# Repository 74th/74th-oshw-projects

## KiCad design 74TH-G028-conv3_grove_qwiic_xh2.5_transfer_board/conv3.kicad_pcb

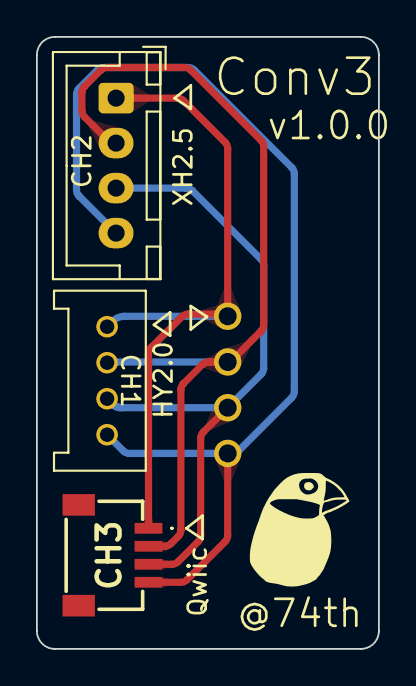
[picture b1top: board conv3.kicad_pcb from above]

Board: 2 copper layers, 19.0 x 34.0 mm, 4 parts (0 on the bottom side), 4 nets.

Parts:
CH1: 4Pin; HY2.0_Socket_TH_4Pin
CH2: 4Pin; JST_XH_B4B-XH-A_1x04_P2.50mm_Vertical
CH3: 4Pin; Qwick_connector
CH4: 4Pin

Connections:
/1: CH1.1, CH2.1, CH3.1, CH4.1
/2: CH1.2, CH2.2, CH3.2, CH4.2
/3: CH1.3, CH2.3, CH3.3, CH4.3
/4: CH1.4, CH2.4, CH3.4, CH4.4

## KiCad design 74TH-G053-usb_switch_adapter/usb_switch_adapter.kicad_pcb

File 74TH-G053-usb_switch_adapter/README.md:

# USB Switch Adapter

Switchable adapter for 5V USB-C devices that allows power shutdown with a switch.

スイッチで、電源遮断によるオフが行える 5V USB-C デバイスのアダプタ

🎥 https://twitter.com/74th/status/1823146532520239136

## feature

- Uses CH217 as the power switch.
- Can be used with CherryMX compatible switches or Kailh Choc Switches commonly used in custom keyboards, allowing for very light key presses.
- Pressing the switch can turn off the power. Additionally, holding down the switch can maintain the power-off state.
- Functions as a resettable fuse for overcurrent protection of 2A or higher. Overcurrent is indicated by LED flashing.
- Used WCH CH32V003J4M6 as the microcontroller. Various functionalities can be added by rewriting the firmware.

### 🇯🇵

- 電源スイッチとして、CH217 を使用。
- スイッチとして、自作キーボードで使われる CherryMX 互換スイッチ、または Kailh Choc Switch を使用可能で、非常に軽い力で押せるようにもできる。
- スイッチ押下で電源断ができる。さらにスイッチ長押しで電源断の状態を継続できる。
- 2A 以上の過電流によるリセッタフューズとしても機能する（2A）。過電流自は、LED が点滅する。
- 制御マイコンとして、WCH CH32V003J4M6 を使用。ファームウェアを書き換えることで、様々な機能を追加できる。

## 1.1.0

- Semantics [PDF](./usb_switch_adapter-semantics-1.1.0.pdf) [Kicanvas](https://kicanvas.org/?github=https%3A%2F%2Fgithub.com%2F74th%2F74th-oshw-projects%2Fblob%2F125ec0107b9b35aba094cce666c352a432412de6%2F74TH-G053-usb_switch_adapter%2Fusb_switch_adapter.kicad_sch)
- PCB [Kicanvas](https://kicanvas.org/?github=https%3A%2F%2Fgithub.com%2F74th%2F74th-oshw-projects%2Fblob%2Fusb-switch-adapter%2F1.1.0%2Fusb_switch_adapter%2Fusb_switch_adapter.kicad_pcb)

## BOM

| Reference | Name                                             | Quantity |
| --------- | ------------------------------------------------ | -------- |
| C1        | Capacitor 0603 100nF                             | 1        |
| D1        | LED 0805 Blue                                    | 1        |
| J1        | USB Type-C Receptacle                            | 1        |
| J2        | USB Type-C Receptacle                            | 1        |
| R1        | Register 0603 30kΩ                               | 1        |
| R2        | Register 0603 10kΩ                               | 1        |
| SW1       | Cheery MX Compatible Switch or Kailh Choc Switch | 1        |
| U1        | USB Power Protection IC SOT-23-6L CH217K         | 1        |
| U2        | MCU SOIC-8 WCH CH32V003J4M6                      | 1        |

## Firmware

- [./firmware/](./firmware/) using ch32v003fun

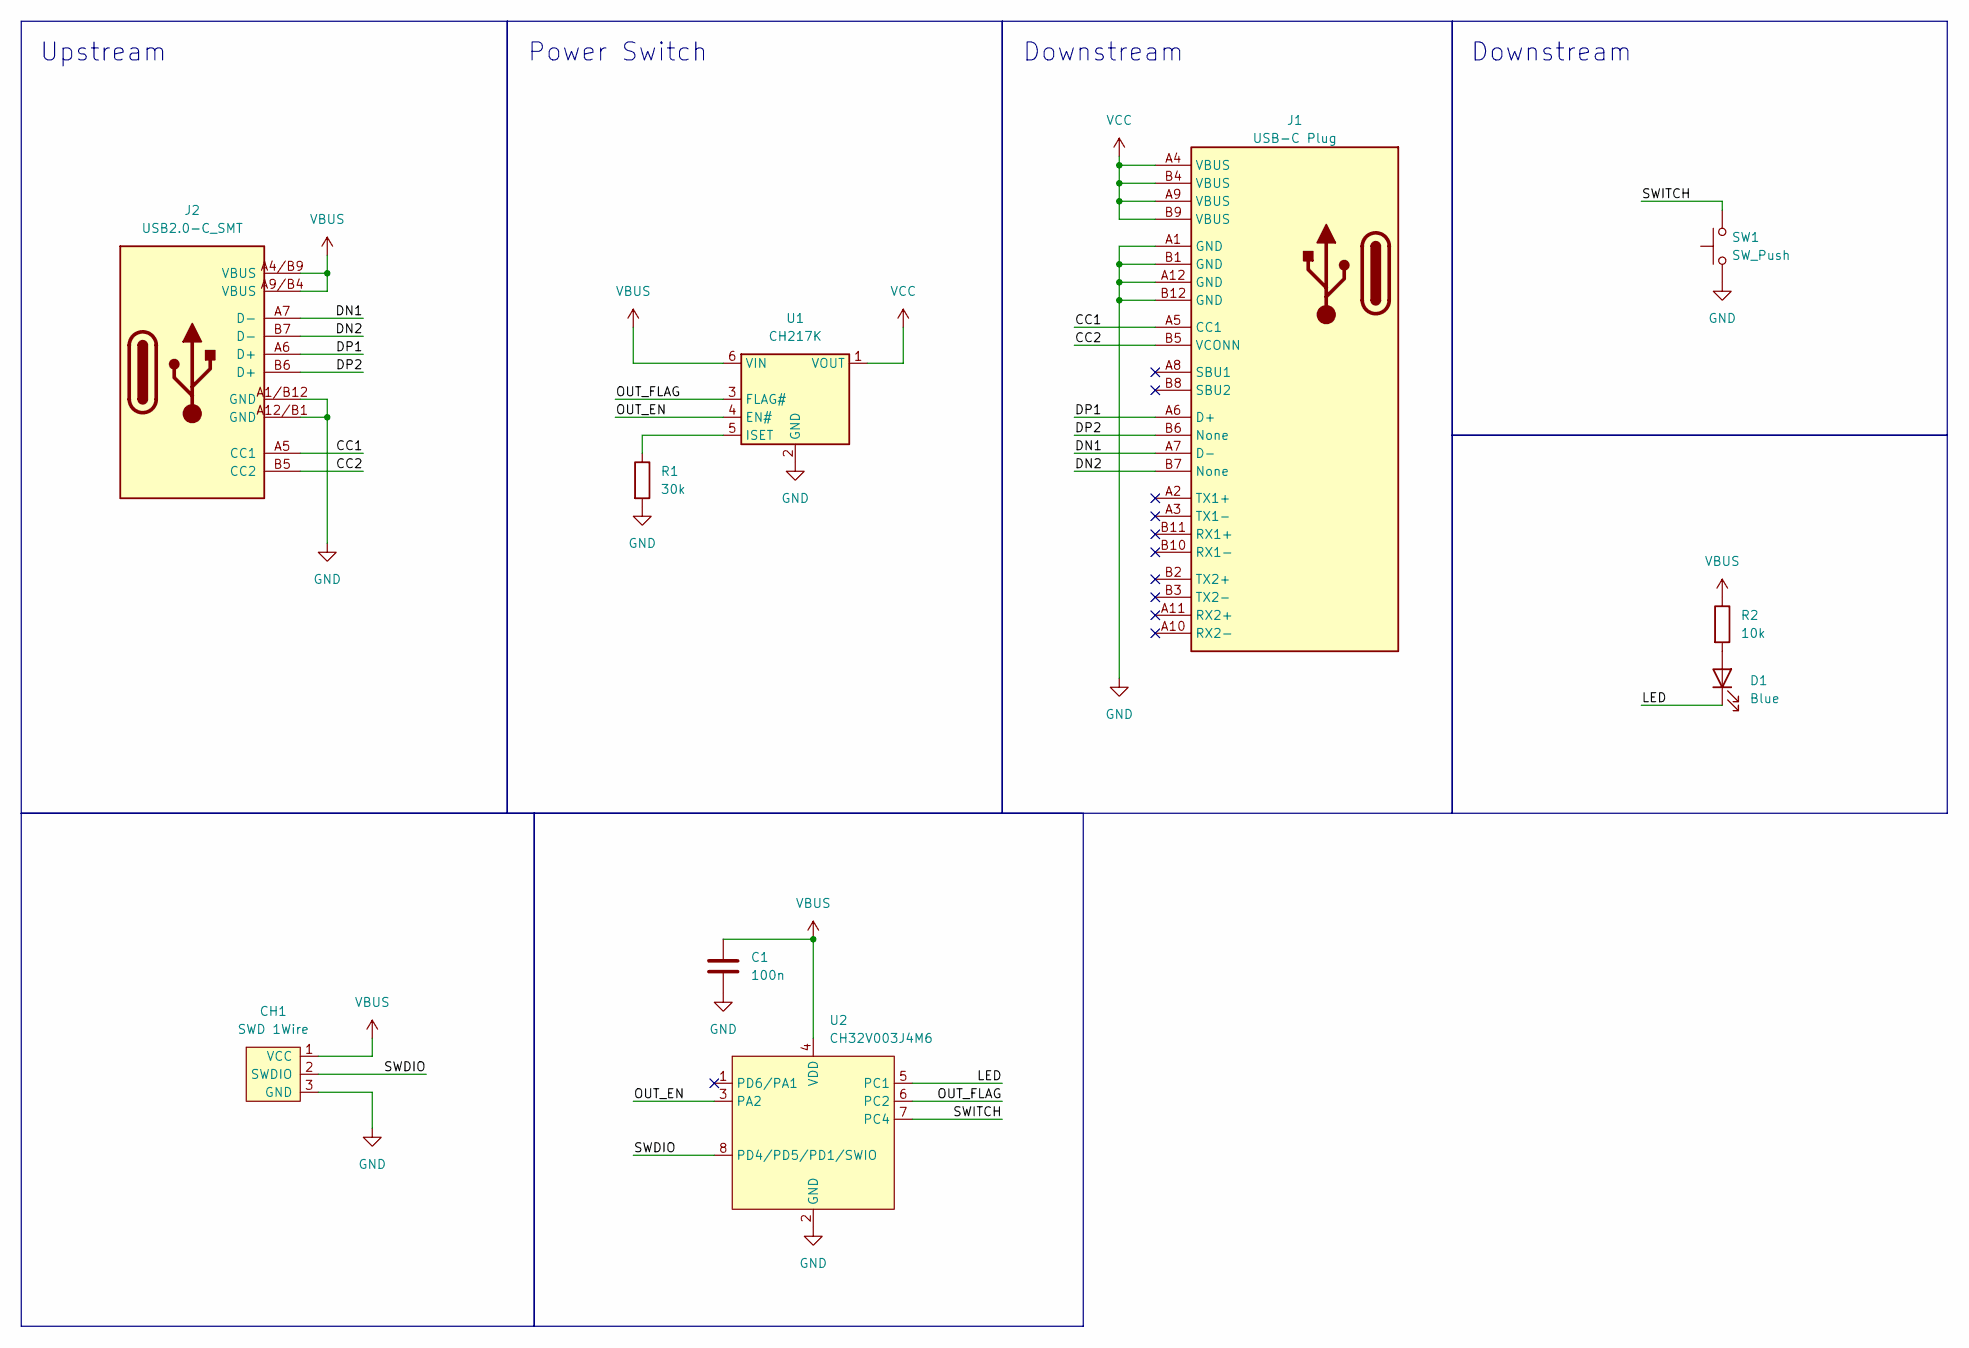
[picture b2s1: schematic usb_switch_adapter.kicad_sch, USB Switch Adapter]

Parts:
C1: 100n; Capacitor_0603_1608
CH1: SWD 1Wire; PinOut_Pin_3_3GND
D1: Blue; LED_BACK_0805_2012
J1: USB-C Plug; Connector_USB-C-Plug_24-Pin
J2: USB2.0-C_SMT; Connector_USB-C-Receptacle_SMT_12-Pin_MidMount
R1: 30k; Register_0603_1608
R2: 10k; Register_0603_1608
SW1: SW_Push; Switch_MXChoc_1.0u
U1: CH217K; Package_SOT-23-6
U2: CH32V003J4M6; Package_SOIC-8_3.9x4.9mm_P1.27mm

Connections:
/CC1: J1.A5 (CC1), J2.A5 (CC1)
/CC2: J1.B5 (VCONN), J2.B5 (CC2)
/DN1: J1.A7 (D-), J2.A7 (D-)
/DN2: J1.B7 (None), J2.B7 (D-)
/DP1: J1.A6 (D+), J2.A6 (D+)
/DP2: J1.B6 (None), J2.B6 (D+)
/LED: D1.1 (K), U2.5 (PC1)
/OUT_EN: U1.4 (EN#), U2.3 (PA2)
/OUT_FLAG: U1.3 (FLAG#), U2.6 (PC2)
/SWDIO: CH1.2 (SWDIO), U2.8 (PD4/PD5/PD1/SWIO)
/SWITCH: SW1.2, U2.7 (PC4)
/TXD: U2.1 (PD6/PA1)
GND: C1.2, CH1.3 (GND), J1.A1 (GND), J1.A12 (GND), J1.B1 (GND), J1.B12 (GND), J2.A1/B12 (GND), J2.A12/B1 (GND), R1.2, SW1.1, U1.2 (GND), U2.2 (GND)
unnamed: D1.2 (A), R2.2
unnamed: R1.1, U1.5 (ISET)
VBUS: C1.1, CH1.1 (VCC), J2.A4/B9 (VBUS), J2.A9/B4 (VBUS), R2.1, U1.6 (VIN), U2.4 (VDD)
VCC: J1.A4 (VBUS), J1.A9 (VBUS), J1.B4 (VBUS), J1.B9 (VBUS), U1.1 (VOUT)

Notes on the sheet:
Power Switch
Downstream
Upstream

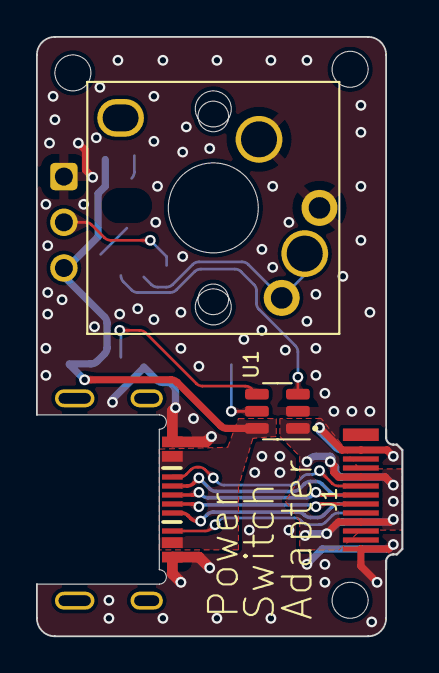
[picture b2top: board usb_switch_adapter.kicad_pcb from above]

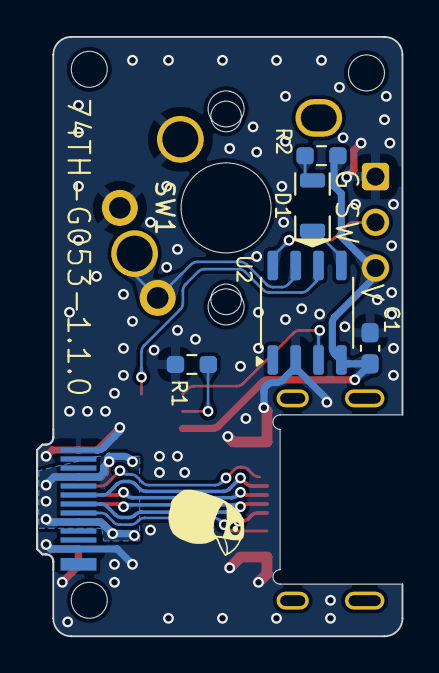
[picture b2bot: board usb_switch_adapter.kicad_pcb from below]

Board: 2 copper layers, 20.3 x 33.3 mm, 14 parts (6 on the bottom side), 16 nets.

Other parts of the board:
M2, M2#2, M2#3: Hole_M2_2.0
MISC-ICON: LOGO; Logo_74th_5mm

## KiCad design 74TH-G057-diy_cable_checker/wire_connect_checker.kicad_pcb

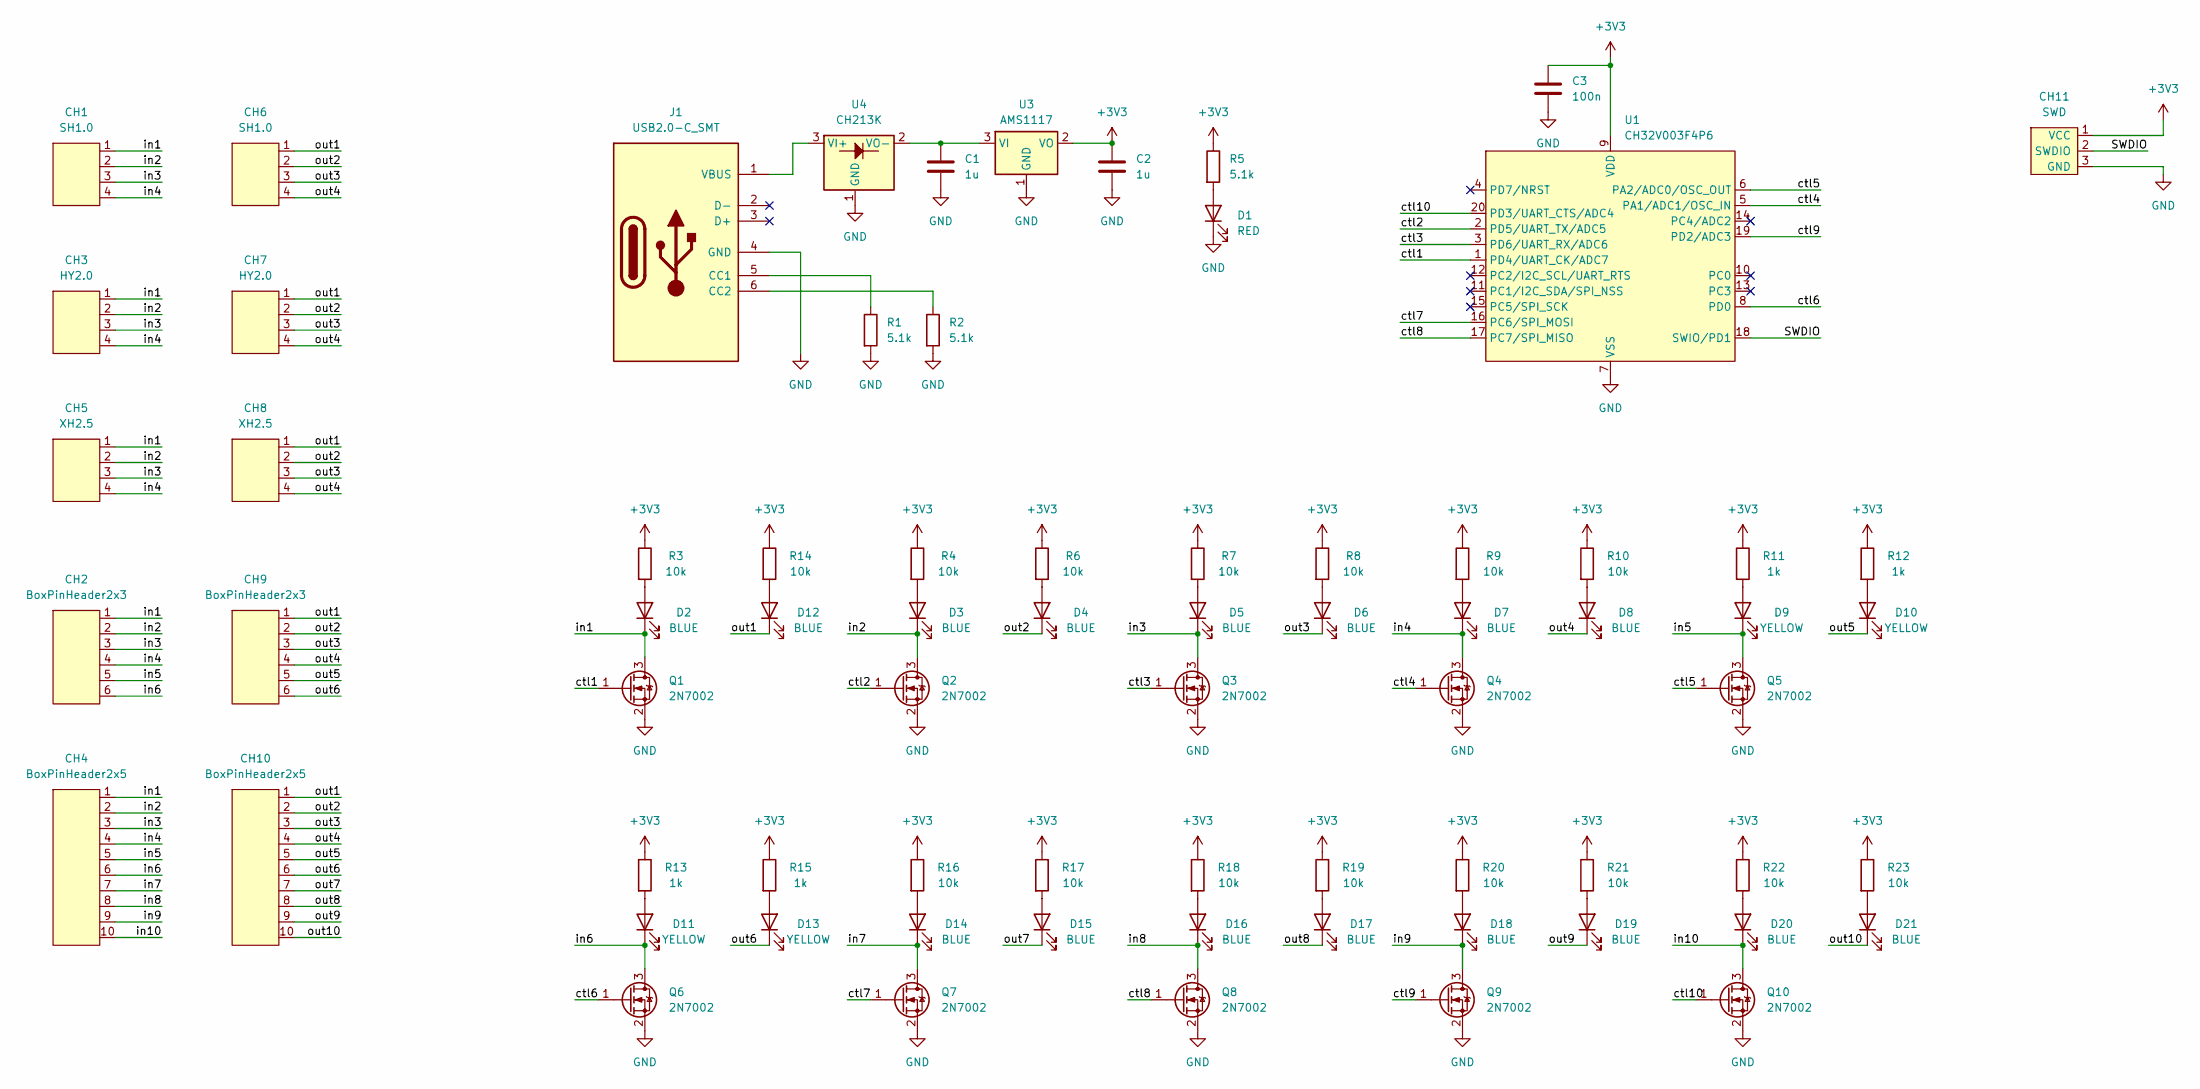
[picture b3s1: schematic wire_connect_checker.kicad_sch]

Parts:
C1, C2: 1u; Capacitor_0805_2012
C3: 100n; Capacitor_0805_2012
CH1, CH6: SH1.0; Connector_SH-1.0_SMD_4Pin
CH2, CH9: BoxPinHeader2x3; Connector_BoxPinHeader_2x03_P1.27mm
CH3, CH7: HY2.0; Connector_HY-2.0_TH-Vertical_4Pin
CH4, CH10: BoxPinHeader2x5; Connector_BoxPinHeader_2x05_P1.27mm
CH5, CH8: XH2.5; JST_XH_B4B-XH-AM_1x04_P2.50mm_Vertical
CH11: SWD; PinOut_Pin_3_3GND
D1: RED; LED_0805_2012
D2, D3, D4, D5, D6, D7, D8, D12, D14, D15, D16, D17, D18, D19, D20, D21: BLUE; LED_0805_2012
D9, D10, D11, D13: YELLOW; LED_0805_2012
J1: USB2.0-C_SMT; Connector_USB-C-Receptacle_SMT_12-Pin_Simple
Q1, Q2, Q3, Q4, Q5, Q6, Q7, Q8, Q9, Q10: 2N7002; Package_SOT-23
R1, R2, R5: 5.1k; Register_0805_2012
R3, R4, R6, R7, R8, R9, R10, R14, R16, R17, R18, R19, R20, R21, R22, R23: 10k; Register_0805_2012
R11, R12, R13, R15: 1k; Register_0805_2012
U1: CH32V003F4P6; Package_TSSOP-20_4.4x6.5mm_P0.65mm
U3: AMS1117; Package_SOT-89-3
U4: CH213K; Package_SOT-23

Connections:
+3V3: C2.1, C3.1, CH11.1 (VCC), R3.1, R4.1, R5.1, R6.1, R7.1, R8.1, R9.1, R10.1, R11.1, R12.1, R13.1, R14.1, R15.1, R16.1, R17.1, R18.1, R19.1, R20.1, R21.1, R22.1, R23.1, U1.9 (VDD), U3.2 (VO)
/SWDIO: CH11.2 (SWDIO), U1.18 (SWIO/PD1)
/ctl1: Q1.1 (G), U1.1 (PD4/UART_CK/ADC7)
/ctl2: Q2.1 (G), U1.2 (PD5/UART_TX/ADC5)
/ctl3: Q3.1 (G), U1.3 (PD6/UART_RX/ADC6)
/ctl4: Q4.1 (G), U1.5 (PA1/ADC1/OSC_IN)
/ctl5: Q5.1 (G), U1.6 (PA2/ADC0/OSC_OUT)
/ctl6: Q6.1 (G), U1.8 (PD0)
/ctl7: Q7.1 (G), U1.16 (PC6/SPI_MOSI)
/ctl8: Q8.1 (G), U1.17 (PC7/SPI_MISO)
/ctl9: Q9.1 (G), U1.19 (PD2/ADC3)
/ctl10: Q10.1 (G), U1.20 (PD3/UART_CTS/ADC4)
/in1: CH1.1, CH2.1, CH3.1, CH4.1, CH5.1, D2.1 (K), Q1.3 (D)
/in2: CH1.2, CH2.2, CH3.2, CH4.2, CH5.2, D3.1 (K), Q2.3 (D)
/in3: CH1.3, CH2.3, CH3.3, CH4.3, CH5.3, D5.1 (K), Q3.3 (D)
/in4: CH1.4, CH2.4, CH3.4, CH4.4, CH5.4, D7.1 (K), Q4.3 (D)
/in5: CH2.5, CH4.5, D9.1 (K), Q5.3 (D)
/in6: CH2.6, CH4.6, D11.1 (K), Q6.3 (D)
/in7: CH4.7, D14.1 (K), Q7.3 (D)
/in8: CH4.8, D16.1 (K), Q8.3 (D)
/in9: CH4.9, D18.1 (K), Q9.3 (D)
/in10: CH4.10, D20.1 (K), Q10.3 (D)
/out1: CH6.1, CH7.1, CH8.1, CH9.1, CH10.1, D12.1 (K)
/out2: CH6.2, CH7.2, CH8.2, CH9.2, CH10.2, D4.1 (K)
/out3: CH6.3, CH7.3, CH8.3, CH9.3, CH10.3, D6.1 (K)
/out4: CH6.4, CH7.4, CH8.4, CH9.4, CH10.4, D8.1 (K)
/out5: CH9.5, CH10.5, D10.1 (K)
/out6: CH9.6, CH10.6, D13.1 (K)
/out7: CH10.7, D15.1 (K)
/out8: CH10.8, D17.1 (K)
/out9: CH10.9, D19.1 (K)
/out10: CH10.10, D21.1 (K)
GND: C1.2, C2.2, C3.2, CH11.3 (GND), D1.1 (K), J1.4 (GND), Q1.2 (S), Q2.2 (S), Q3.2 (S), Q4.2 (S), Q5.2 (S), Q6.2 (S), Q7.2 (S), Q8.2 (S), Q9.2 (S), Q10.2 (S), R1.2, R2.2, U1.7 (VSS), U3.1 (GND), U4.1 (GND)
unnamed: D1.2 (A), R5.2
unnamed: D2.2 (A), R3.2
unnamed: D3.2 (A), R4.2
unnamed: D4.2 (A), R6.2
unnamed: D5.2 (A), R7.2
unnamed: D6.2 (A), R8.2
unnamed: D7.2 (A), R9.2
unnamed: D8.2 (A), R10.2
unnamed: D9.2 (A), R11.2
unnamed: D10.2 (A), R12.2
unnamed: D11.2 (A), R13.2
unnamed: D12.2 (A), R14.2
unnamed: D13.2 (A), R15.2
unnamed: D14.2 (A), R16.2
unnamed: D15.2 (A), R17.2
unnamed: D16.2 (A), R18.2
unnamed: D17.2 (A), R19.2
unnamed: D18.2 (A), R20.2
unnamed: D19.2 (A), R21.2
unnamed: D20.2 (A), R22.2
unnamed: D21.2 (A), R23.2
unnamed: J1.5 (CC1), R1.1
unnamed: J1.6 (CC2), R2.1
unnamed: J1.1 (VBUS), U4.3 (VI+)
unnamed: C1.1, U3.3 (VI), U4.2 (VO-)

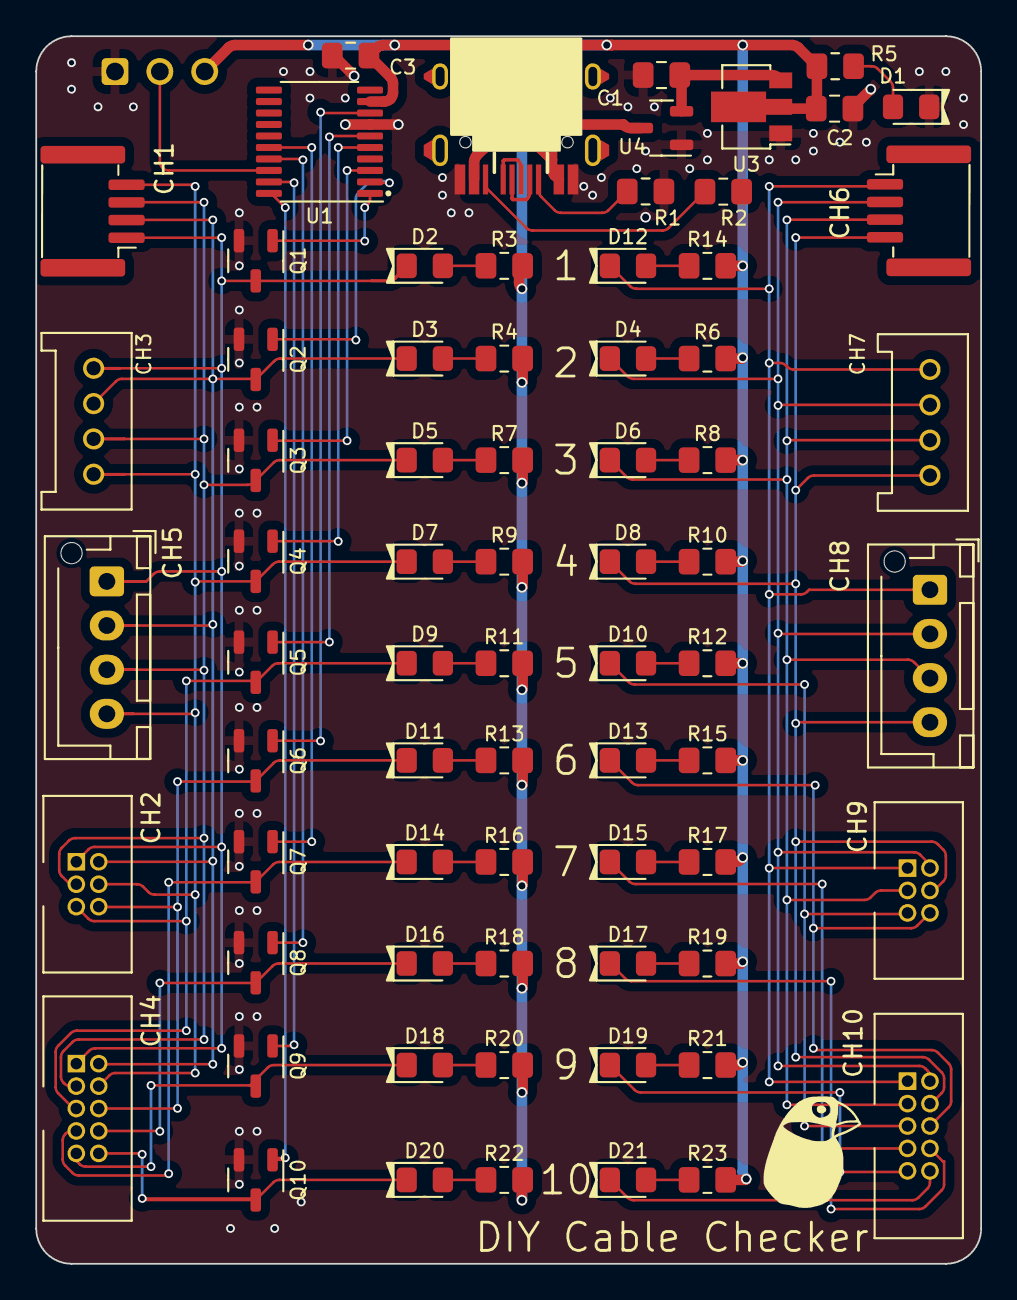
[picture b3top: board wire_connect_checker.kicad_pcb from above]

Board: 2 copper layers, 53.5 x 69.5 mm, 73 parts (0 on the bottom side), 58 nets.

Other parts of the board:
MISC-ICON: LOGO; 74th-7.5mm

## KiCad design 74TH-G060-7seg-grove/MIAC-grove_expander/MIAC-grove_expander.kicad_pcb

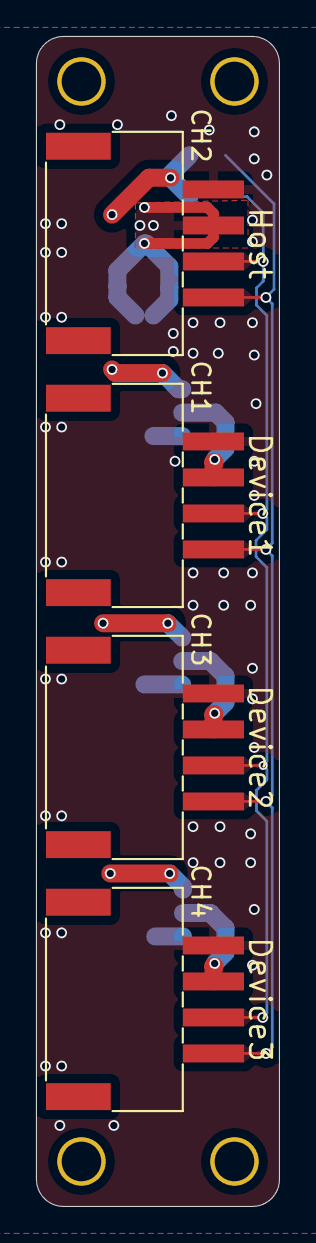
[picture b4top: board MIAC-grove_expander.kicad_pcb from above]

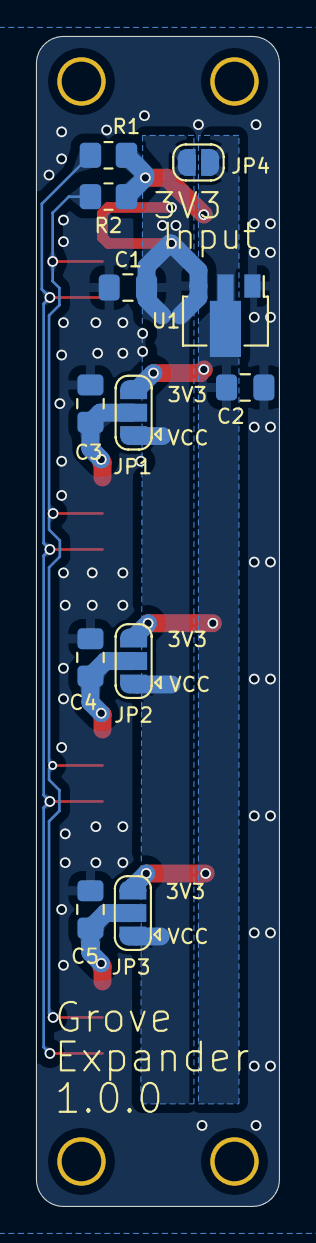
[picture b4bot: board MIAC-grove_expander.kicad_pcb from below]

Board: 2 copper layers, 13.5 x 65.0 mm, 20 parts (12 on the bottom side), 8 nets.

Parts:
C1, C2, C3, C4, C5: 22u; Capacitor_0805_2012
CH1: Device1; Connector_HY-2.0_SMD_4Pin
CH2: Host; Connector_HY-2.0_SMD_4Pin
CH3: Device2; Connector_HY-2.0_SMD_4Pin
CH4: Device3; Connector_HY-2.0_SMD_4Pin
JP1, JP2, JP3: Jumper_3_Open; SolderJumper-3
JP4: Jumper_2_Open; SolderJumper-2
M2, M2#2, M2#3, M2#4: M2_v2
R1, R2: 1k; Register_0805_2012
U1: AMS1117; Package_SOT-89-3

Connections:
+3V3: C2.1, JP1.3 (B), JP2.3 (B), JP3.3 (B), JP4.1 (A), R1.1, R2.1, U1.2 (VO)
/D1: CH1.1 (D0), CH2.1 (SCL), CH3.1 (D0), CH4.1 (D0), R1.2
/D2: CH1.2 (D1), CH2.2 (SDA), CH3.2 (D1), CH4.2 (D1), R2.2
GND: C1.2, C2.2, C3.2, C4.2, C5.2, CH1.4 (GND), CH2.4 (GND), CH3.4 (GND), CH4.4 (GND), U1.1 (GND)
unnamed: C3.1, CH1.3 (VCC), JP1.2 (C)
unnamed: C4.1, CH3.3 (VCC), JP2.2 (C)
unnamed: C5.1, CH4.3 (VCC), JP3.2 (C)
VCC: C1.1, CH2.3 (VCC), JP1.1 (A), JP2.1 (A), JP3.1 (A), JP4.2 (B), U1.3 (VI)

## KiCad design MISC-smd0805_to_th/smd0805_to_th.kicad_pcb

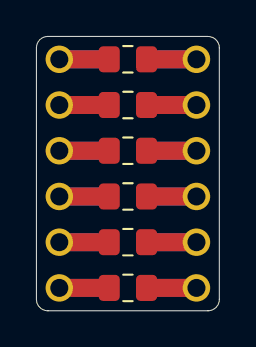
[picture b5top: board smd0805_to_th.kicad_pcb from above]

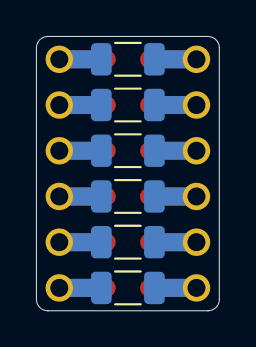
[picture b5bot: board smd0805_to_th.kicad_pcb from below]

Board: 2 copper layers, 10.2 x 15.2 mm, 14 parts (6 on the bottom side), 12 nets.

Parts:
CH1, CH2: Pin_6; PinOut_Pin_6
R1, R2, R3, R4, R5, R6: R; Capacitor_0805_2012
R7, R8, R9, R10, R11, R12: R; Capacitor_1206_3216

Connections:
unnamed: CH1.1, R1.1, R7.1
unnamed: CH1.2, R2.1, R8.1
unnamed: CH1.3, R3.1, R9.1
unnamed: CH1.4, R4.1, R10.1
unnamed: CH1.5, R5.1, R11.1
unnamed: CH1.6, R6.1, R12.1
unnamed: CH2.1, R1.2, R7.2
unnamed: CH2.2, R2.2, R8.2
unnamed: CH2.3, R3.2, R9.2
unnamed: CH2.4, R4.2, R10.2
unnamed: CH2.5, R5.2, R11.2
unnamed: CH2.6, R6.2, R12.2

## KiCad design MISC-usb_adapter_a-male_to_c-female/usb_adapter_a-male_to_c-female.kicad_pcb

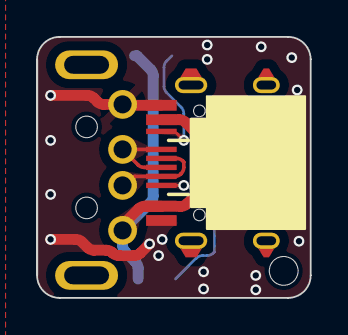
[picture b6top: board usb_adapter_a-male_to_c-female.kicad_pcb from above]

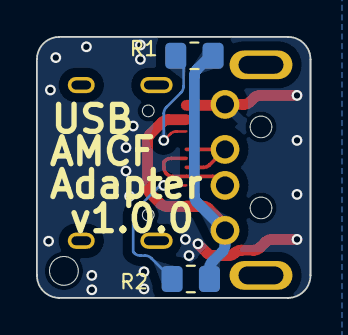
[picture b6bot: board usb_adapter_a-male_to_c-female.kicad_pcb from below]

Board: 2 copper layers, 15.2 x 14.5 mm, 5 parts (2 on the bottom side), 6 nets.

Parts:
J1: USB_TypeA-2.0_Plug; Connector_USB-A-Plug_TH
J2: USB2.0-C_SMT; Connector_USB-C-Receptacle_SMT_12-Pin_Simple
M2: Hole_M1.6_1.6
R1, R2: 56k; Register_0805_2012

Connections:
GND: J1.4 (GND), J2.4 (GND)
unnamed: J1.3 (D+), J2.3 (D+)
unnamed: J1.2 (D-), J2.2 (D-)
unnamed: J1.1 (VBUS), J2.1 (VBUS), R1.1, R2.1
unnamed: J2.5 (CC1), R2.2
unnamed: J2.6 (CC2), R1.2

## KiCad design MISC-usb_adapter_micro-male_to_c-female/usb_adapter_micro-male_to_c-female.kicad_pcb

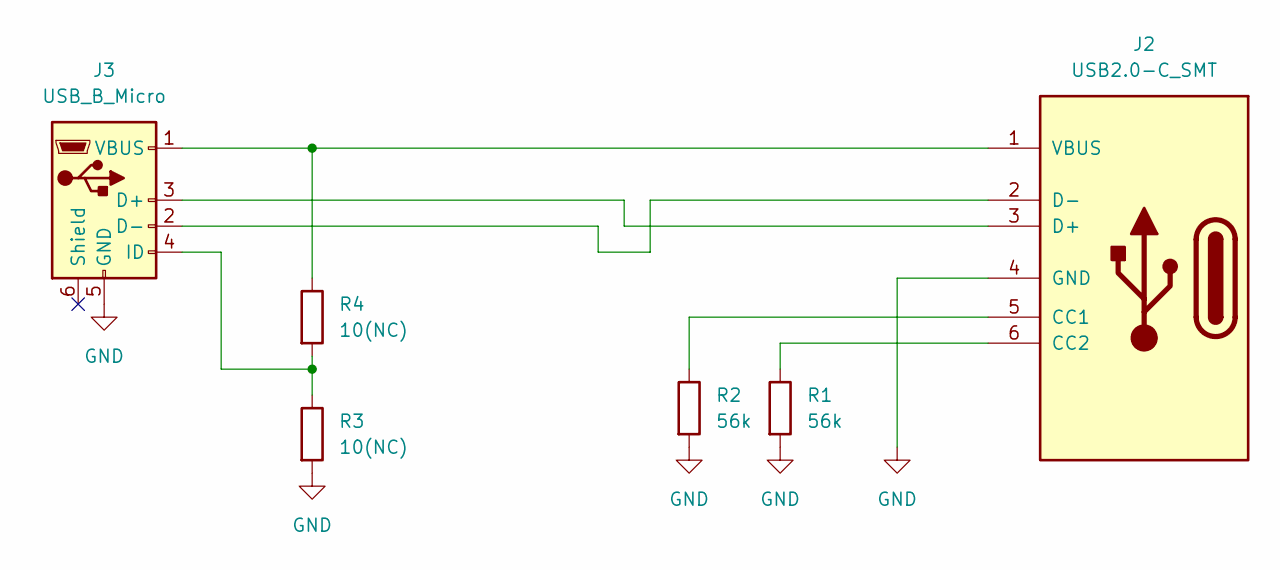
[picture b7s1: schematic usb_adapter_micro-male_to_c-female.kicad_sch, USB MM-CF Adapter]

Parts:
J2: USB2.0-C_SMT; Connector_USB-C-Receptacle_SMT_12-Pin_Simple
J3: USB_B_Micro; Connector_USB-Micro-Plug_SMD
R1, R2: 56k; Register_0603_1608
R3, R4: 10(NC); Register_0603_1608

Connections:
GND: J2.4 (GND), J3.5 (GND), R1.2, R2.2, R3.2
unnamed: J2.5 (CC1), R2.1
unnamed: J2.6 (CC2), R1.1
unnamed: J2.3 (D+), J3.3 (D+)
unnamed: J2.2 (D-), J3.2 (D-)
unnamed: J2.1 (VBUS), J3.1 (VBUS), R4.1
unnamed: J3.4 (ID), R3.1, R4.2

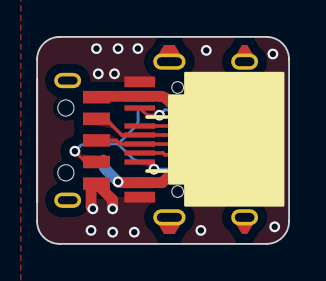
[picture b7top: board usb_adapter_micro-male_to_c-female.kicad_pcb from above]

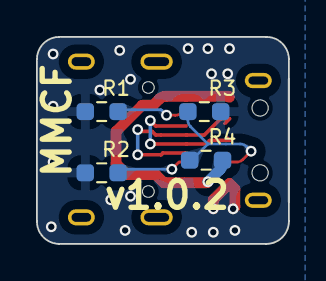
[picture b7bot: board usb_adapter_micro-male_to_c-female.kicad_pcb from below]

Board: 2 copper layers, 14.0 x 11.5 mm, 6 parts (4 on the bottom side), 7 nets.

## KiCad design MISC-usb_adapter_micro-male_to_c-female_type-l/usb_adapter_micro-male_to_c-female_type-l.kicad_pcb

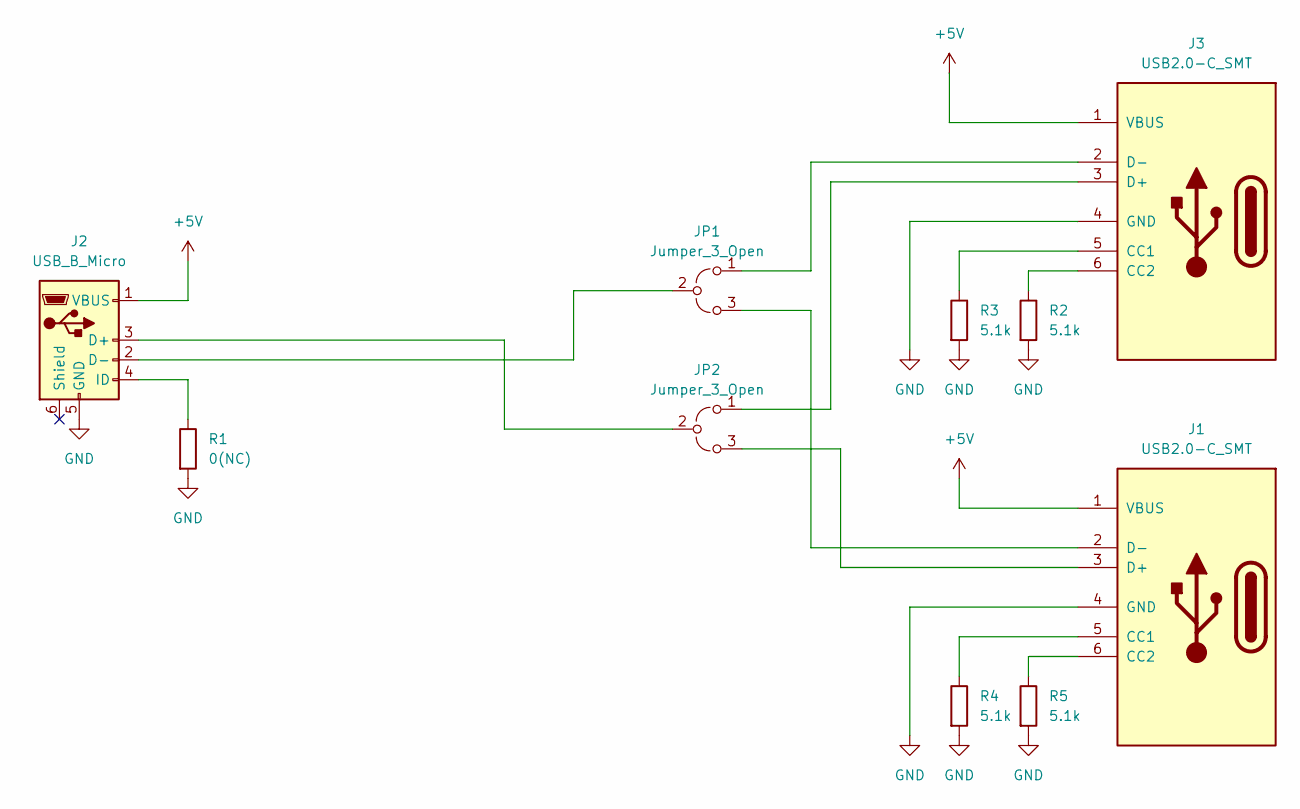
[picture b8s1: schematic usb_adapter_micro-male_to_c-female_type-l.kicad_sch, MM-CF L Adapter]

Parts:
J1, J3: USB2.0-C_SMT; Connector_USB-C-Receptacle_SMT_12-Pin_Simple
J2: USB_B_Micro; Connector_USB-Micro-Plug_SMD
JP1, JP2: Jumper_3_Open; SolderJumper-3_No1PinMark
R1: 0(NC); Register_0603_1608
R2, R3, R4, R5: 5.1k; Register_0603_1608

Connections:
+5V: J1.1 (VBUS), J2.1 (VBUS), J3.1 (VBUS)
GND: J1.4 (GND), J2.5 (GND), J3.4 (GND), R1.2, R2.2, R3.2, R4.2, R5.2
unnamed: J1.5 (CC1), R4.1
unnamed: J1.6 (CC2), R5.1
unnamed: J1.3 (D+), JP2.3 (B)
unnamed: J1.2 (D-), JP1.3 (B)
unnamed: J2.3 (D+), JP2.2 (C)
unnamed: J2.2 (D-), JP1.2 (C)
unnamed: J2.4 (ID), R1.1
unnamed: J3.5 (CC1), R3.1
unnamed: J3.6 (CC2), R2.1
unnamed: J3.3 (D+), JP2.1 (A)
unnamed: J3.2 (D-), JP1.1 (A)

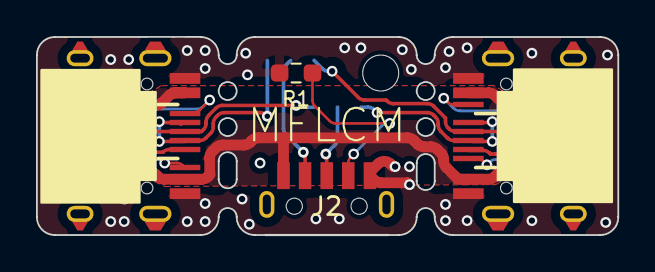
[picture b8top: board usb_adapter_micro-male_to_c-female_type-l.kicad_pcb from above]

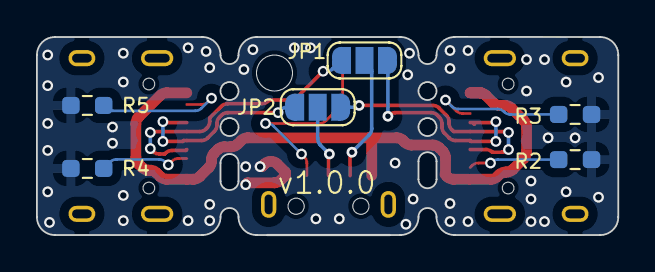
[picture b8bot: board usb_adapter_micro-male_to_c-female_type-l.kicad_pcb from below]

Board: 2 copper layers, 32.3 x 11.0 mm, 11 parts (6 on the bottom side), 13 nets.

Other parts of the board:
M1: Hole_M2_2.0
